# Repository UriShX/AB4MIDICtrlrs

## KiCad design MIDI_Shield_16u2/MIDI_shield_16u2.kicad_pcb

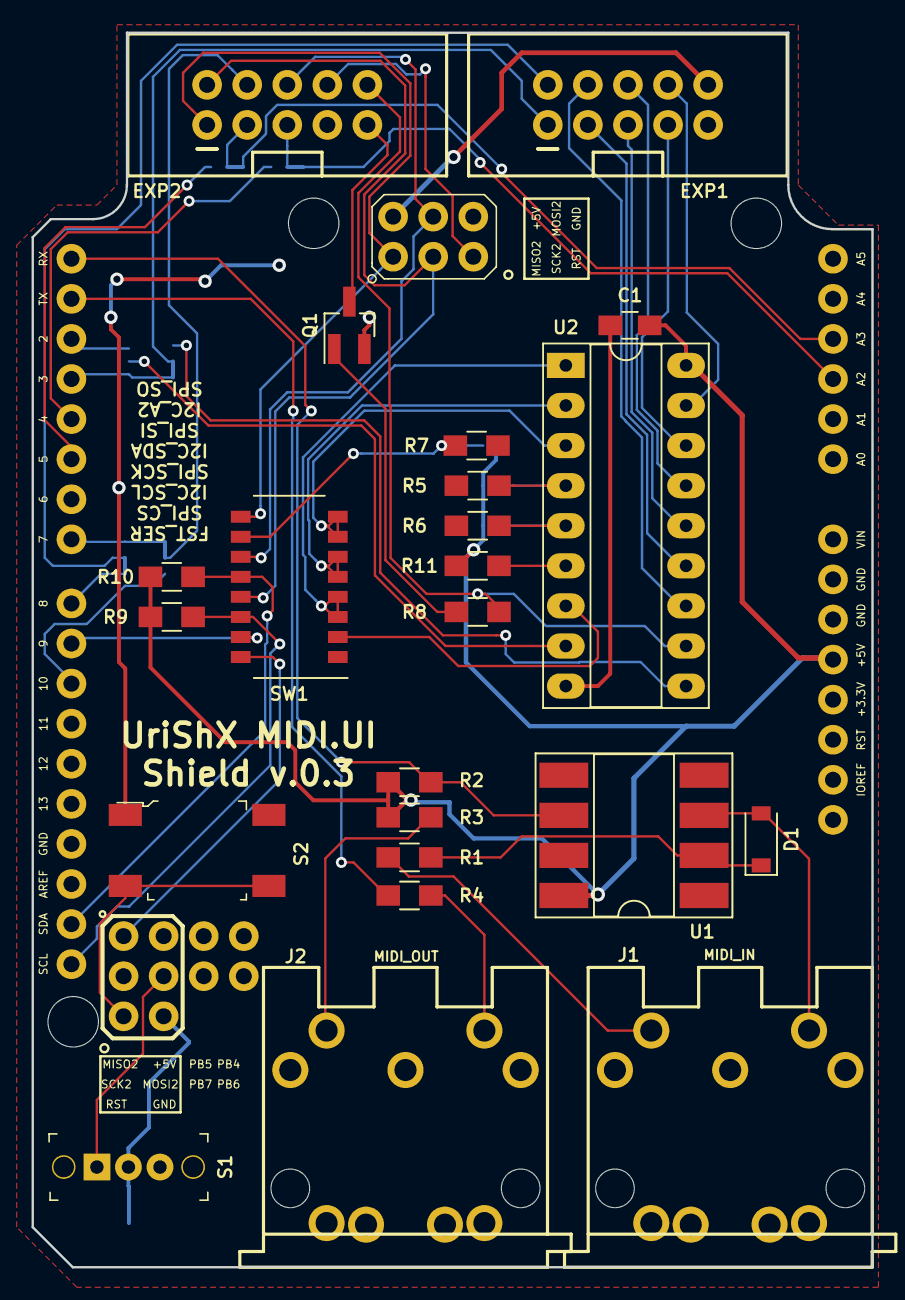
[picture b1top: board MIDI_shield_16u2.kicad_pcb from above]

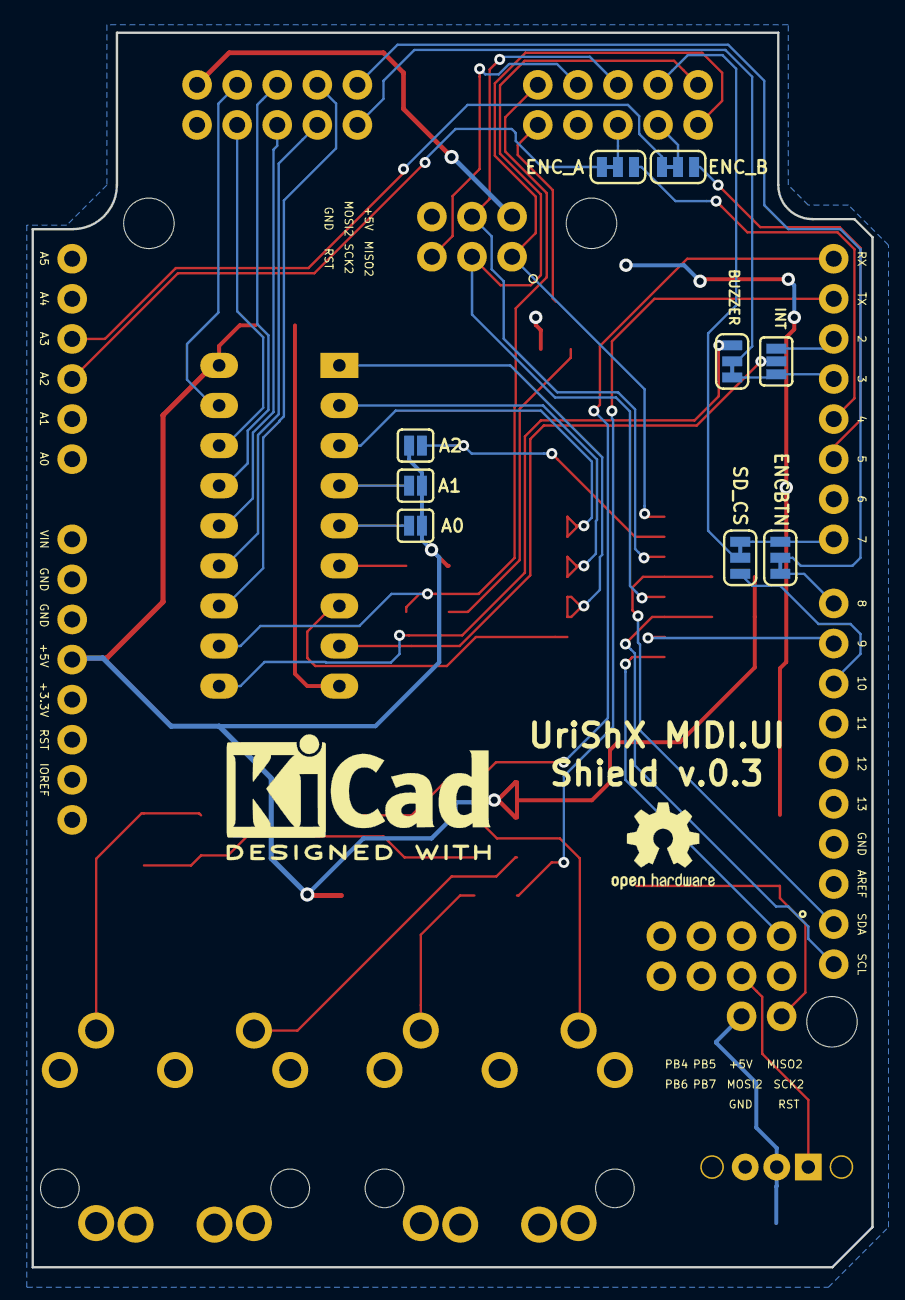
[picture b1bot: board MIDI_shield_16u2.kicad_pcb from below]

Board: 2 copper layers, 53.2 x 78.2 mm, 33 parts (9 on the bottom side), 52 nets.

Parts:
B2: ARDUINO_UNO_R3_SHIELD_ICSP_16u2_BREAKOUT; UNO_R3_SHIELD_16u2_BREAKOUT_wHoles
C1: 0.1UF-0603-25V-_+80_-20%_; C_0805_HandSoldering
D1: 1N4148; D_SOD-123
EXP1, EXP2: CONN_05X2SHD; 2X5-SHROUDED
J1: MIDI_IN; DIN5-RA-PTH
J2: MIDI_OUT; DIN5-RA-PTH
JP1: INT; SMT-JUMPER_3_NO_SILK
JP2: ENC_A; SMT-JUMPER_3_1-NC_TRACE_SILK
JP3: ENC_B; SMT-JUMPER_3_1-NC_TRACE_SILK
JP4: ENCBTN; SMT-JUMPER_3_1-NC_TRACE_SILK
JP5: BUZZER; SMT-JUMPER_3_1-NC_TRACE_SILK
JP6: A0; SMT-JUMPER_2_NO_SILK
JP7: SD_CS; SMT-JUMPER_3_1-NC_TRACE_SILK
JP8: A1; SMT-JUMPER_2_NO_SILK
JP9: A2; SMT-JUMPER_2_NO_SILK
Q1: Q_NPN_BEC_2222A; SOT-23_Handsoldering
R1, R2, R3, R4: 220R_1_4W_5%; R_0805_HandSoldering
R5, R6, R7, R8, R11: 10k_1_4W_5%; R_0805_HandSoldering
R9, R10: 4K7_1_4W_5%; R_0805_HandSoldering
S1: SWITCH-SPDT-SMD-RIGHT-ANGLE; Switch_Slide_Right_Angle_8.6X4.4mm_C&K_OS102011MA1QS1
S2: MOMENTARY-SWITCH-SPST-2-SMD-5.2MM; Switch_Tact_SMD_6x6mm
SW1: SW_DIP_x08; SW_DIP_x8_W6.15mm_Slide_Omron_A6H
U1: OPTO_DARL_6N138S; DIP-8_W8.89mm_SMDSocket_LongPads
U2: MCP23S08; DIP-18_W7.62mm_Socket_LongPads

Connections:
/16U2_RSTJP: B2.SI_2, S1.1
/ARDUINO_RST: B2.RES, B2.RST, EXP2.8
/BUZZER: EXP1.1, JP5.2
/BUZZER_: JP5.1, U2.10
/ENC_A: EXP2.5, JP2.2
/ENC_A_NC: B2.A2, JP2.3
/ENC_A_NO: B2.D4, JP2.1
/ENC_B: EXP2.3, JP3.2
/ENC_BTN: EXP1.2, JP4.2
/ENC_BTN_NC: B2.D8, JP4.3
/ENC_B_NC: B2.A3, JP3.3
/ENC_B_NO: B2.D5, JP3.1
/EXPANDER_CS: SW1.2, U2.7
/EXT_INT0: B2.D2, JP1.3
/EXT_INT1: B2.D3, JP1.1, JP5.3
/FAST_SERIAL: B2.SO_2, SW1.16
/GND_CTL: EXP2.10, R8.2, U2.11
/LCD4: EXP1.5, U2.14
/LCD5: EXP1.6, U2.15
/LCD6: EXP1.7, U2.16
/LCD7: EXP1.8, U2.17
/LCD&BUZZER_CS: B2.D9, SW1.15
/LCDE: EXP1.3, U2.13
/LCDRS: EXP1.4, U2.12
/LCD_GND_CTL: EXP2.9, Q1.3
/MIDI_IN: B2.RX, R2.1, U1.6
/MIDI_OUT: B2.TX, R4.2
/MISO_: B2.D12, B2.MISO, EXP2.1, SW1.9
/MOSI_: B2.D11, B2.MOSI, EXP2.6, SW1.11
/SCK_: B2.D13, B2.SCK, EXP2.2, SW1.13
/SCL: B2.SCL, R9.2, SW1.14
/SDA: B2.SDA, R10.2, SW1.12
/SD_CS: EXP2.4, JP7.2
/SD_CS_NC/ENC_BTN_NO: B2.D7, JP4.1, JP7.3
/SD_CS_NO: B2.D10, JP7.1
GND: B2.GND2, B2.GND@, B2.GND_, C1.2, EXP1.9, J2.2, Q1.2, R5.2, R6.2, R7.2, S1.2, S2.1, S2.2, SW1.1, U1.5, U2.9
unnamed: B2.RST2, S2.3, S2.4
unnamed: D1.1, R1.2, U1.2
unnamed: D1.2, J1.4, U1.3
unnamed: J1.5, R1.1
unnamed: J2.4, R4.1
unnamed: J2.5, R3.1
unnamed: JP1.2, U2.8
unnamed: JP6.1, R6.1, U2.5
unnamed: JP8.1, R5.1, U2.4
unnamed: JP9.2, R7.1, SW1.10
unnamed: Q1.1, R8.1
unnamed: R11.2, U2.6
unnamed: SW1.3, SW1.4, U2.1
unnamed: SW1.5, SW1.6, U2.2
unnamed: SW1.7, SW1.8, U2.3
VCC: B2.5V, B2.5V_1, B2.5V_2, C1.1, EXP1.10, JP6.2, JP8.2, JP9.1, R2.2, R3.2, R9.1, R10.1, R11.1, U1.8, U2.18

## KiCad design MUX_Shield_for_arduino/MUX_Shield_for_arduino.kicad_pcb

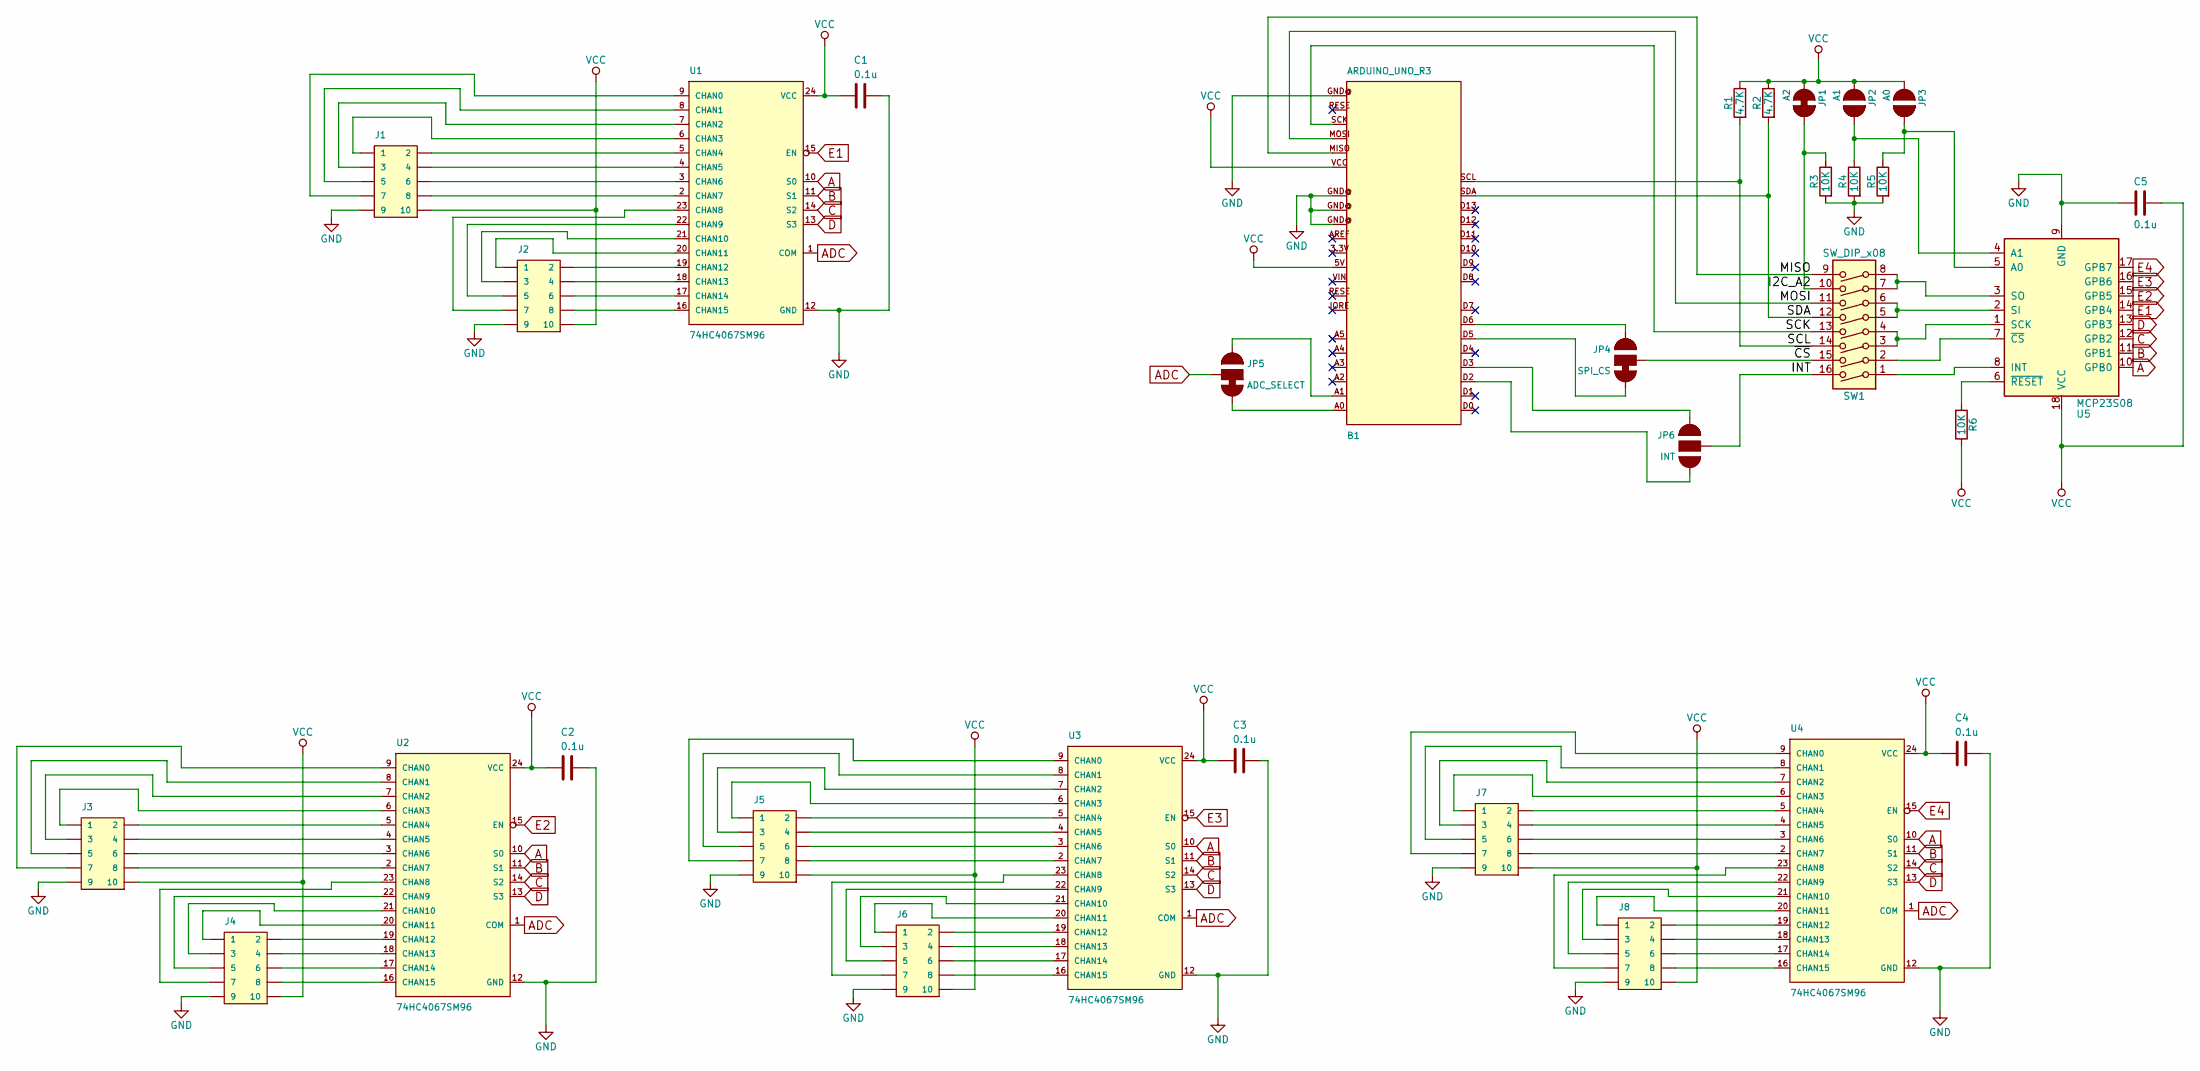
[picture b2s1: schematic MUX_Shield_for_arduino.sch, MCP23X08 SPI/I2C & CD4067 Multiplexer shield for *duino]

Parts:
B1: ARDUINO_UNO_R3; ARDUINO_R3
C1, C2, C3, C4, C5: 0.1u; C_0805_HandSoldering
J1, J2, J3, J4, J5, J6, J7, J8: CONN_05X20.05_IN_PTH_SILK; 2X5-SHROUDED
JP1: A2; SMT-JUMPER_2_NC_TRACE_SILK
JP2: A1; SMT-JUMPER_2_NO_SILK
JP3: A0; SMT-JUMPER_2_NO_SILK
JP4: SPI_CS; SMT-JUMPER_3_1-NC_TRACE_SILK
JP5: ADC_SELECT; SMT-JUMPER_3_1-NC_TRACE_SILK
JP6: INT; SMT-JUMPER_3_NO_SILK
R1, R2: 4.7K; R_0805_HandSoldering
R3, R4, R5, R6: 10K; R_0805_HandSoldering
SW1: SW_DIP_x08; SW_DIP_x8_W6.15mm_Slide_Omron_A6H
U1, U2, U3, U4: 74HC4067SM96; SOIC-24W_7.5x15.4mm_Pitch1.27mm
U5: MCP23S08; DIP-18_W7.62mm_Socket_LongPads

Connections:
/I2C_A2: JP1.2, R3.1, SW1.10
/INT: JP6.2, SW1.16
/MISO: B1.MISO, SW1.9
/MOSI: B1.MOSI, SW1.11
/SCK: B1.SCK, SW1.13
/SCL: B1.SCL, R1.2, SW1.14
/SDA: B1.SDA, R2.2, SW1.12
/~CS: JP4.2, SW1.15
A: U1.10 (S0), U2.10 (S0), U3.10 (S0), U4.10 (S0), U5.10 (GPB0)
ADC: JP5.2, U1.1 (COM), U2.1 (COM), U3.1 (COM), U4.1 (COM)
B: U1.11 (S1), U2.11 (S1), U3.11 (S1), U4.11 (S1), U5.11 (GPB1)
C: U1.14 (S2), U2.14 (S2), U3.14 (S2), U4.14 (S2), U5.12 (GPB2)
D: U1.13 (S3), U2.13 (S3), U3.13 (S3), U4.13 (S3), U5.13 (GPB3)
E1: U1.15 (EN), U5.14 (GPB4)
E2: U2.15 (EN), U5.15 (GPB5)
E3: U3.15 (EN), U5.16 (GPB6)
E4: U4.15 (EN), U5.17 (GPB7)
GND: B1.GND@ (GND), C1.1, C2.1, C3.1, C4.1, C5.2, J1.9, J2.9, J3.9, J4.9, J5.9, J6.9, J7.9, J8.9, R3.2, R4.2, R5.2, U1.12 (GND), U2.12 (GND), U3.12 (GND), U4.12 (GND), U5.9 (GND)
unnamed: B1.A0, JP5.3
unnamed: B1.A1, JP5.1
unnamed: B1.D2, JP6.3
unnamed: B1.D3 (*D3), JP6.1
unnamed: B1.D5 (*D5), JP4.3
unnamed: B1.D6 (*D6), JP4.1
unnamed: J1.1, U1.6 (CHAN3)
unnamed: J1.2, U1.5 (CHAN4)
unnamed: J1.3, U1.7 (CHAN2)
unnamed: J1.4, U1.4 (CHAN5)
unnamed: J1.5, U1.8 (CHAN1)
unnamed: J1.6, U1.3 (CHAN6)
unnamed: J1.7, U1.9 (CHAN0)
unnamed: J1.8, U1.2 (CHAN7)
unnamed: J2.1, U1.20 (CHAN11)
unnamed: J2.2, U1.19 (CHAN12)
unnamed: J2.3, U1.21 (CHAN10)
unnamed: J2.4, U1.18 (CHAN13)
unnamed: J2.5, U1.22 (CHAN9)
unnamed: J2.6, U1.17 (CHAN14)
unnamed: J2.7, U1.23 (CHAN8)
unnamed: J2.8, U1.16 (CHAN15)
unnamed: J3.1, U2.6 (CHAN3)
unnamed: J3.2, U2.5 (CHAN4)
unnamed: J3.3, U2.7 (CHAN2)
unnamed: J3.4, U2.4 (CHAN5)
unnamed: J3.5, U2.8 (CHAN1)
unnamed: J3.6, U2.3 (CHAN6)
unnamed: J3.7, U2.9 (CHAN0)
unnamed: J3.8, U2.2 (CHAN7)
unnamed: J4.1, U2.20 (CHAN11)
unnamed: J4.2, U2.19 (CHAN12)
unnamed: J4.3, U2.21 (CHAN10)
unnamed: J4.4, U2.18 (CHAN13)
unnamed: J4.5, U2.22 (CHAN9)
unnamed: J4.6, U2.17 (CHAN14)
unnamed: J4.7, U2.23 (CHAN8)
unnamed: J4.8, U2.16 (CHAN15)
unnamed: J5.1, U3.6 (CHAN3)
unnamed: J5.2, U3.5 (CHAN4)
unnamed: J5.3, U3.7 (CHAN2)
unnamed: J5.4, U3.4 (CHAN5)
unnamed: J5.5, U3.8 (CHAN1)
unnamed: J5.6, U3.3 (CHAN6)
unnamed: J5.7, U3.9 (CHAN0)
unnamed: J5.8, U3.2 (CHAN7)
unnamed: J6.1, U3.20 (CHAN11)
unnamed: J6.2, U3.19 (CHAN12)
unnamed: J6.3, U3.21 (CHAN10)
unnamed: J6.4, U3.18 (CHAN13)
unnamed: J6.5, U3.22 (CHAN9)
unnamed: J6.6, U3.17 (CHAN14)
unnamed: J6.7, U3.23 (CHAN8)
unnamed: J6.8, U3.16 (CHAN15)
unnamed: J7.1, U4.6 (CHAN3)
unnamed: J7.2, U4.5 (CHAN4)
unnamed: J7.3, U4.7 (CHAN2)
unnamed: J7.4, U4.4 (CHAN5)
unnamed: J7.5, U4.8 (CHAN1)
unnamed: J7.6, U4.3 (CHAN6)
unnamed: J7.7, U4.9 (CHAN0)
unnamed: J7.8, U4.2 (CHAN7)
unnamed: J8.1, U4.20 (CHAN11)
unnamed: J8.2, U4.19 (CHAN12)
unnamed: J8.3, U4.21 (CHAN10)
unnamed: J8.4, U4.18 (CHAN13)
unnamed: J8.5, U4.22 (CHAN9)
unnamed: J8.6, U4.17 (CHAN14)
unnamed: J8.7, U4.23 (CHAN8)
unnamed: J8.8, U4.16 (CHAN15)
unnamed: JP2.2, R4.1, U5.4 (A1)
unnamed: JP3.2, R5.1, U5.5 (A0)
unnamed: R6.2, U5.6 (~RESET)
unnamed: SW1.1, U5.8 (INT)
unnamed: SW1.2, U5.7 (~CS)
unnamed: SW1.3, SW1.4, U5.1 (SCK)
unnamed: SW1.5, SW1.6, U5.2 (SI)
unnamed: SW1.7, SW1.8, U5.3 (SO)
VCC: B1.5V, B1.VCC, C1.2, C2.2, C3.2, C4.2, C5.1, J1.10, J2.10, J3.10, J4.10, J5.10, J6.10, J7.10, J8.10, JP1.1, JP2.1, JP3.1, R1.1, R2.1, R6.1, U1.24 (VCC), U2.24 (VCC), U3.24 (VCC), U4.24 (VCC), U5.18 (VCC)

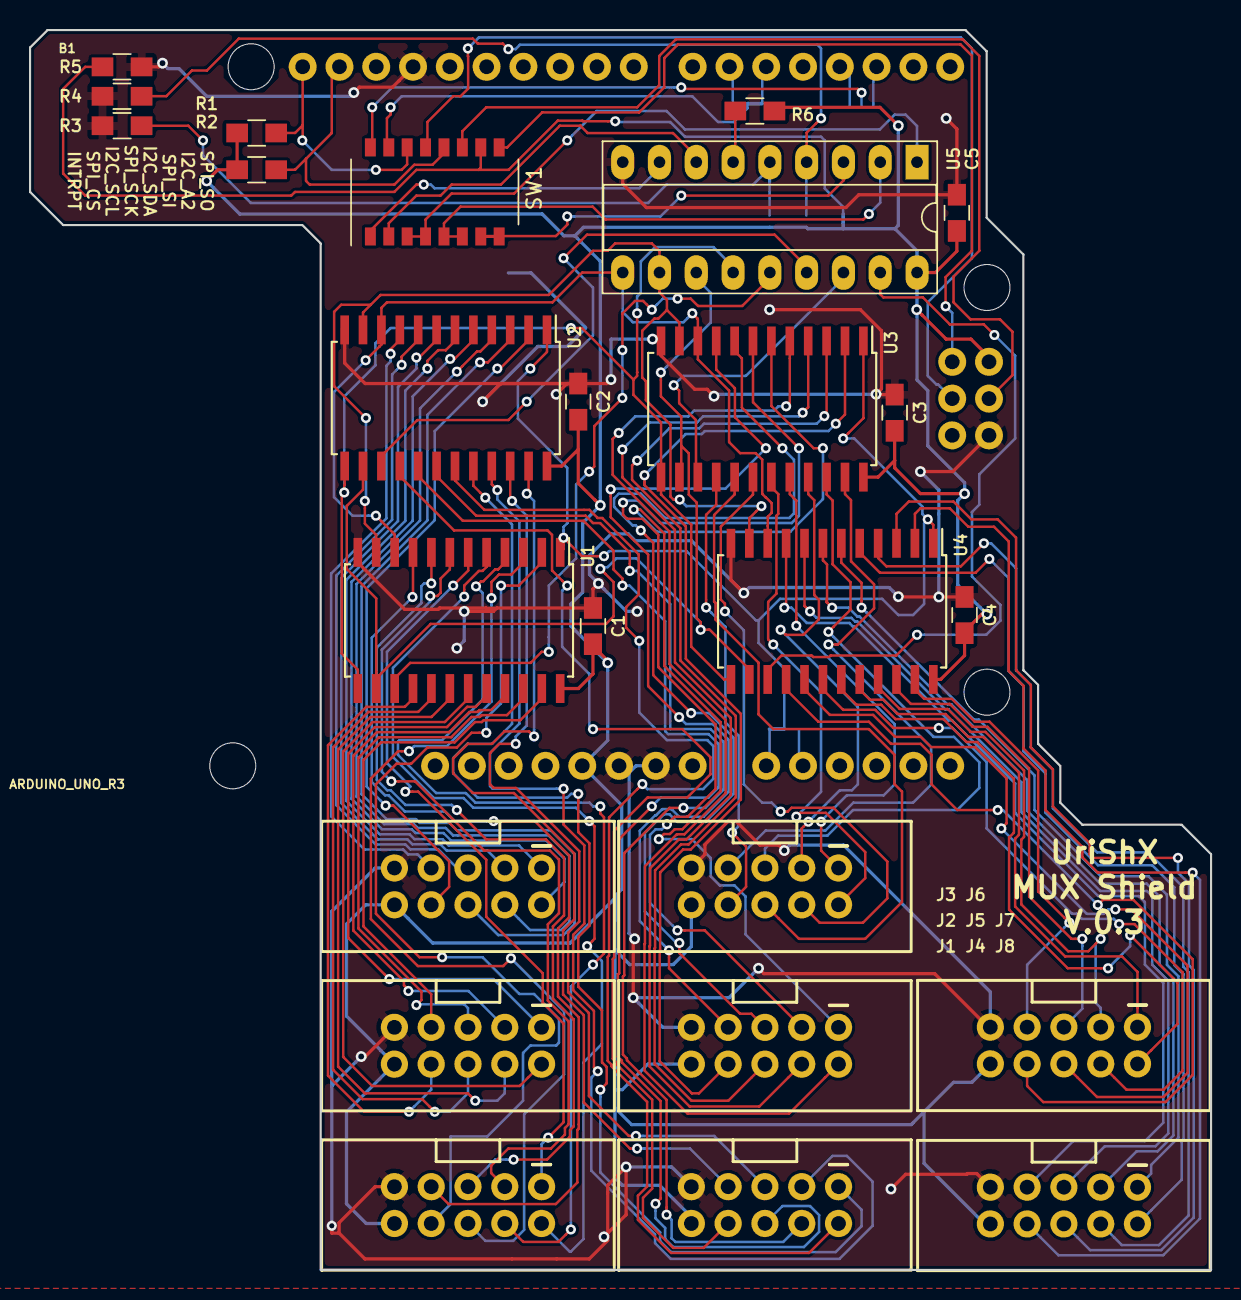
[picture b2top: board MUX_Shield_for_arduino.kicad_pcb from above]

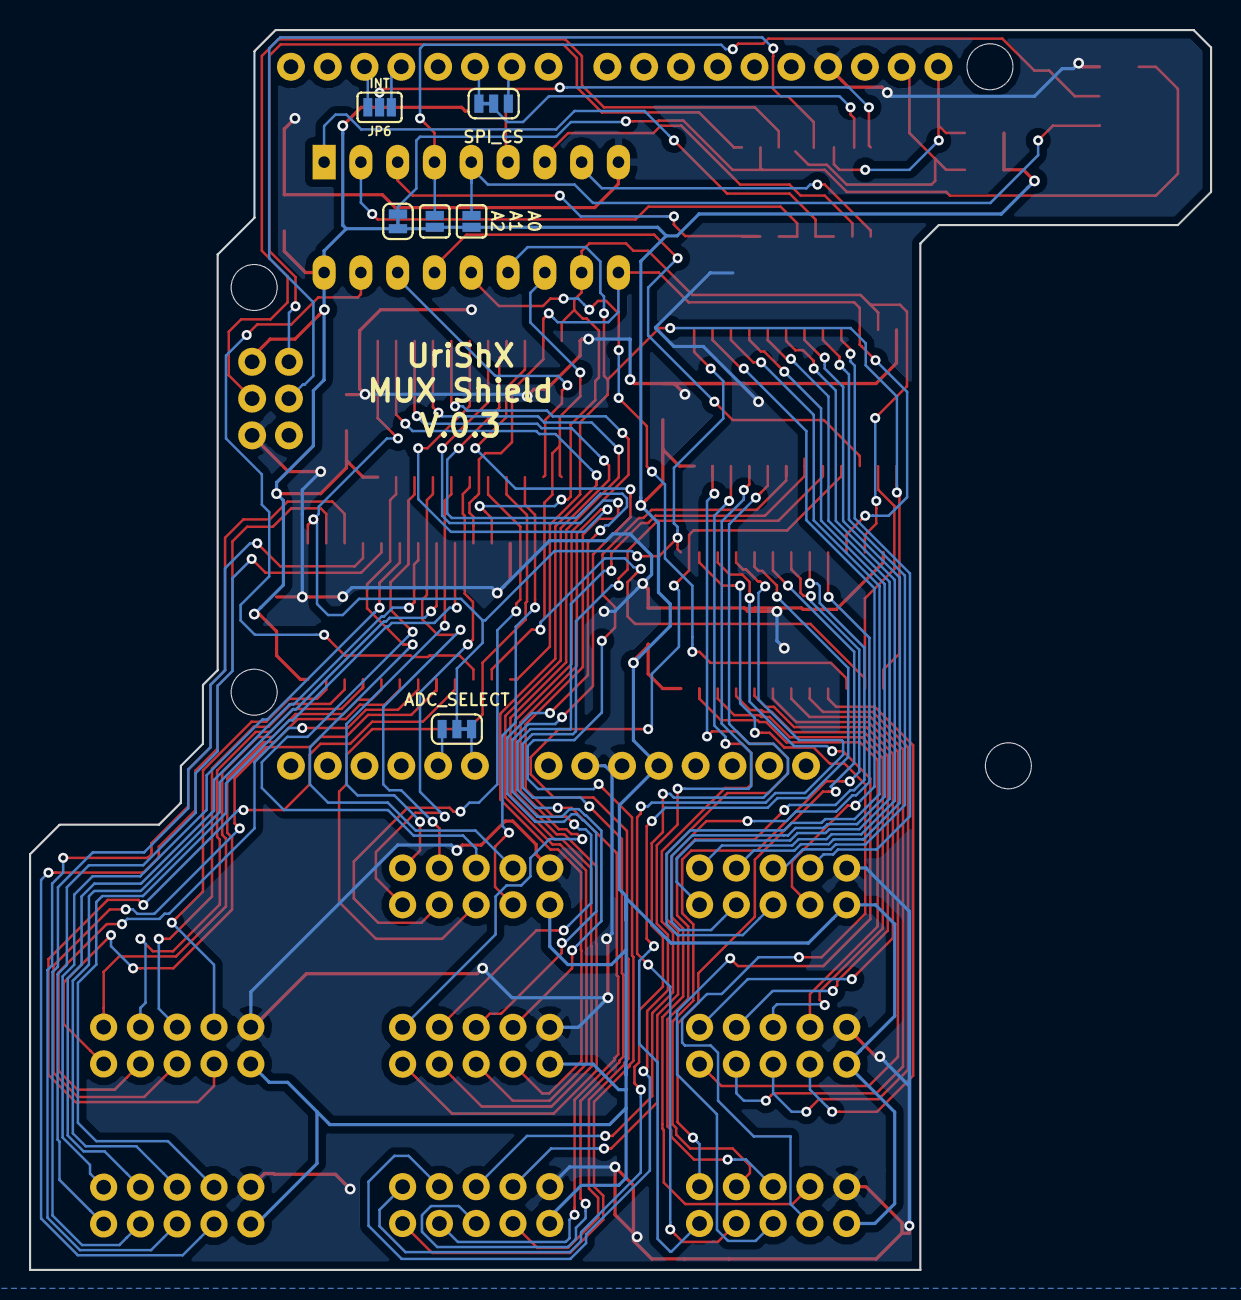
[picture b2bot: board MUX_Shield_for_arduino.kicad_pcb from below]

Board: 2 copper layers, 81.5 x 85.6 mm, 32 parts (6 on the bottom side), 97 nets.

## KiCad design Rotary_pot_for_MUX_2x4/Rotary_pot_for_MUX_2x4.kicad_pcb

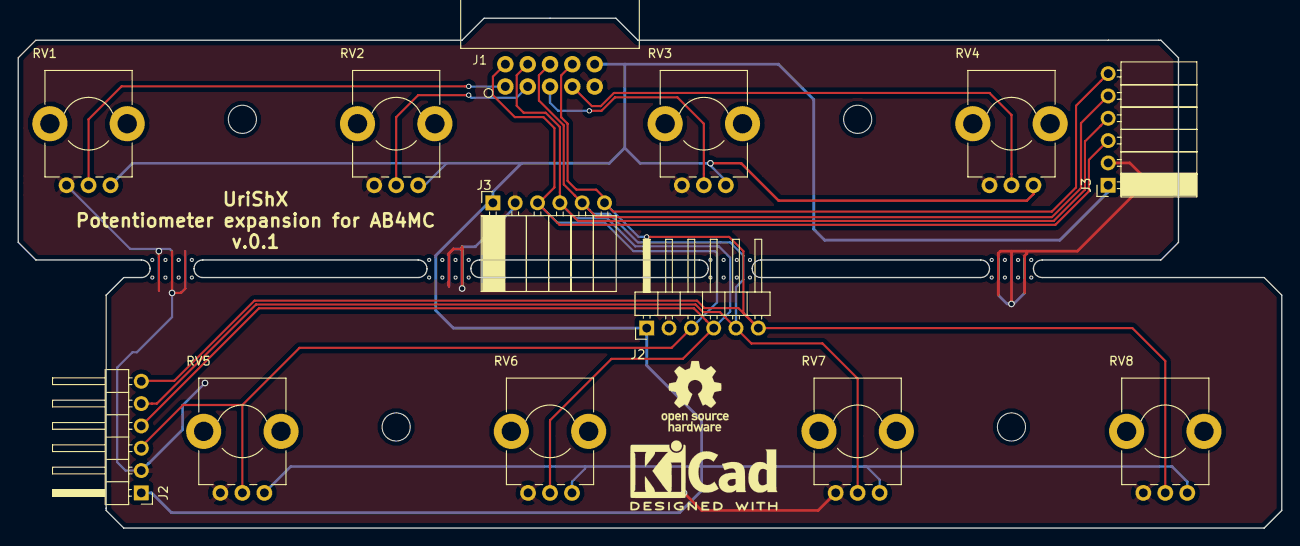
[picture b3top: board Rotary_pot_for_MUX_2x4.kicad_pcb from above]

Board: 2 copper layers, 143.8 x 58.0 mm, 13 parts (0 on the bottom side), 10 nets.

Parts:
J1: Conn_02x05_Odd_Even; 2X5-SHROUDED_rightAngle
J2, J2#2: Conn_01x06_Male; Pin_Header_Angled_1x06_Pitch2.54mm
J3, J3#2: Conn_01x06_Female; Socket_Strip_Angled_1x06_Pitch2.54mm
RV1, RV2, RV3, RV4, RV5, RV6, RV7, RV8: 10k_B; Potentiometer_Bourns_PTV09A_Horizontal

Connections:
GND: J1.9, J2.2, J2#2.2, J3.2, J3#2.2, RV1.1, RV2.1, RV3.1, RV4.1, RV5.1, RV6.1, RV7.1, RV8.1
unnamed: J1.1, RV1.2
unnamed: J1.2, J2.3, J2#2.3, J3.3, J3#2.3, RV5.2
unnamed: J1.3, RV2.2
unnamed: J1.4, J2.4, J2#2.4, J3.4, J3#2.4, RV6.2
unnamed: J1.5, RV3.2
unnamed: J1.6, J2.5, J2#2.5, J3.5, J3#2.5, RV7.2
unnamed: J1.7, RV4.2
unnamed: J1.8, J2.6, J2#2.6, J3.6, J3#2.6, RV8.2
VCC: J1.10, J2.1, J2#2.1, J3.1, J3#2.1, RV1.3, RV2.3, RV3.3, RV4.3, RV5.3, RV6.3, RV7.3, RV8.3

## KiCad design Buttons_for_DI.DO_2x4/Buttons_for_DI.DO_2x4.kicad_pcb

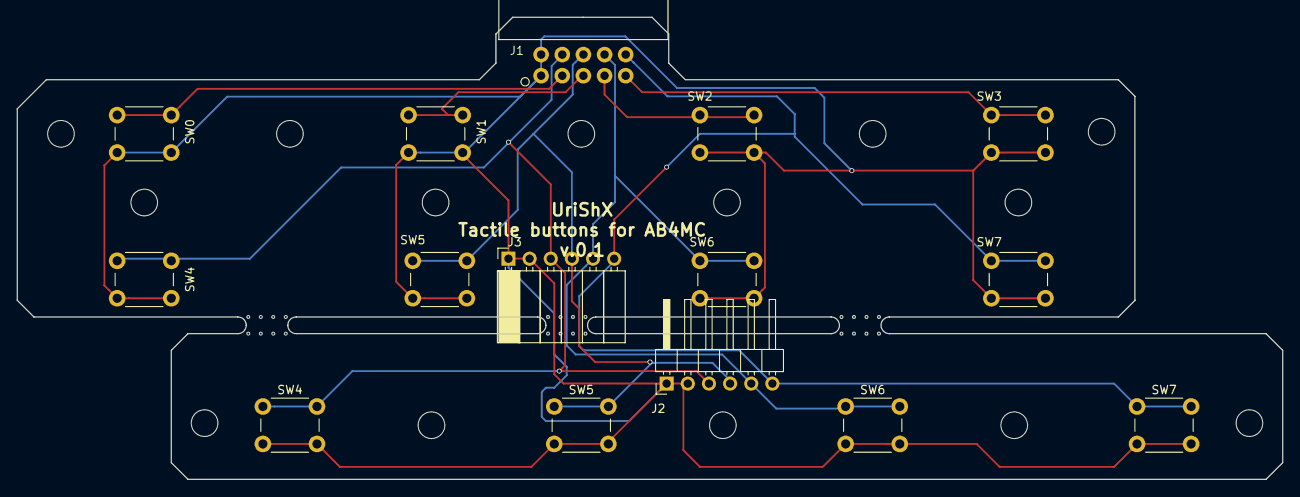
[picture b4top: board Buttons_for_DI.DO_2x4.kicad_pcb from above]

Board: 2 copper layers, 152.0 x 55.5 mm, 15 parts (0 on the bottom side), 9 nets.

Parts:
J1: Conn_02x05_Odd_Even; 2X5-SHROUDED_rightAngle
J2: Conn_01x06_Male; Pin_Header_Angled_1x06_Pitch2.54mm
J3: Conn_01x06_Female; Socket_Strip_Angled_1x06_Pitch2.54mm
SW0, SW1, SW2, SW3, SW4, SW4#2, SW5, SW5#2, SW6, SW6#2, SW7, SW7#2: SW_Push; SW_PUSH_6mm

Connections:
Common_pin: J1.1, J1.2, J2.1, J2.2, J3.1, J3.2, SW0.2, SW1.2, SW2.2, SW3.2, SW4.2, SW4#2.2, SW5.2, SW5#2.2, SW6.2, SW6#2.2, SW7.2, SW7#2.2
unnamed: J1.3, SW0.1
unnamed: J1.4, J2.3, J3.3, SW4.1, SW4#2.1
unnamed: J1.5, SW1.1
unnamed: J1.6, J2.4, J3.4, SW5.1, SW5#2.1
unnamed: J1.7, SW2.1
unnamed: J1.8, J2.5, J3.5, SW6.1, SW6#2.1
unnamed: J1.9, SW3.1
unnamed: J1.10, J2.6, J3.6, SW7.1, SW7#2.1

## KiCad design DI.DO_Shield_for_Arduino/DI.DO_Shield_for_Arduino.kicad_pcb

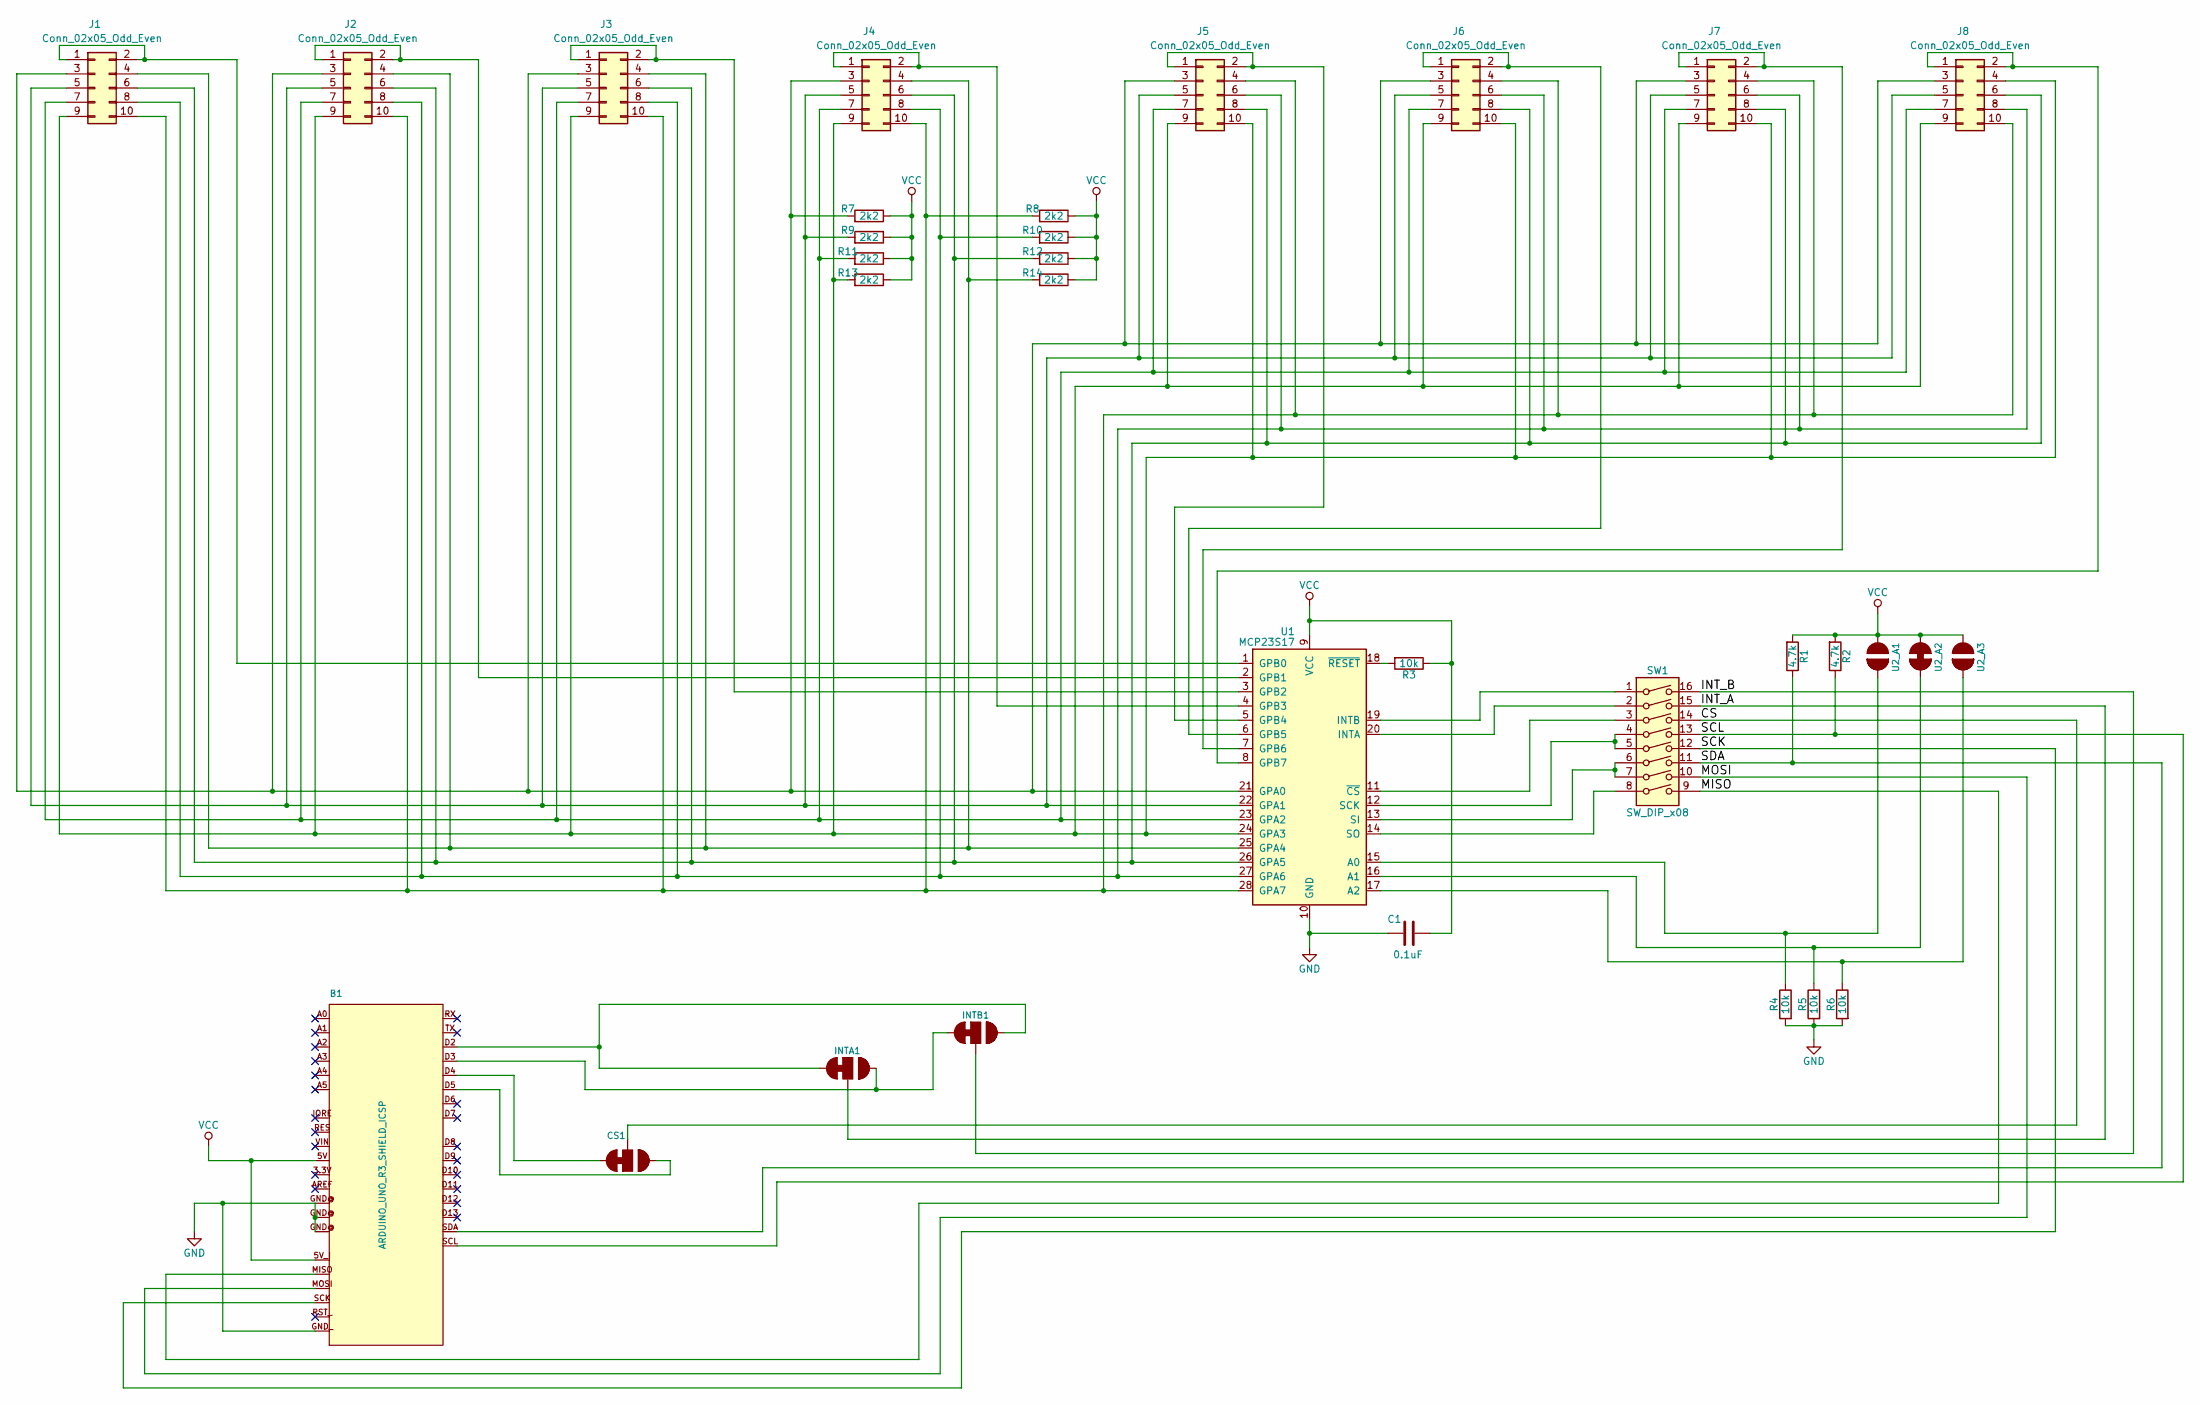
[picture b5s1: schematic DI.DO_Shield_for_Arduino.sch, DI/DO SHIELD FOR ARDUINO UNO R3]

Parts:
B1: ARDUINO_UNO_R3_SHIELD_ICSP; ARDUINO_R3
C1: 0.1uF; C_0805_HandSoldering
CS1: JUMPER-SMT_3_1-NC; SMT-JUMPER_3_1-NC_TRACE_SILK
INTA1: JUMPER-SMT_3_1-NC; SMT-JUMPER_3_1-NC_TRACE_SILK
INTB1: JUMPER-SMT_3_1-NC; SMT-JUMPER_3_1-NC_TRACE_SILK
J1, J2, J3, J4, J5, J6, J7, J8: Conn_02x05_Odd_Even; 2X5-SHROUDED
R1, R2: 4.7k; R_0805_HandSoldering
R3, R4, R5, R6: 10k; R_0805_HandSoldering
R7, R8, R9, R10, R11, R12, R13, R14: 2k2; R_0805_HandSoldering
SW1: SW_DIP_x08; SW_DIP_x8_W6.15mm_Slide_Omron_A6H
U1: MCP23S17; DIP-28_W7.62mm_LongPads
U2_A1, U2_A3: JUMPER-SMT_2_NO; SMT-JUMPER_2_NO_SILK
U2_A2: JUMPER-SMT_2_NC; SMT-JUMPER_2_NC_TRACE_SILK

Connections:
/CS: CS1.2, SW1.14
/INT_A: INTA1.2, SW1.15
/INT_B: INTB1.2, SW1.16
/MISO: B1.MISO, SW1.9
/MOSI: B1.MOSI, SW1.10
/SCK: B1.SCK, SW1.12
/SCL: B1.SCL, R2.1, SW1.13
/SDA: B1.SDA, R1.1, SW1.11
GND: B1.GND@ (GND), B1.GND_ (GND), C1.1, R4.2, R5.2, R6.2, U1.10 (GND)
unnamed: B1.D2, INTA1.3, INTB1.1
unnamed: B1.D3 (*D3), INTA1.1, INTB1.3
unnamed: B1.D4, CS1.3
unnamed: B1.D5 (*D5), CS1.1
unnamed: J1.1, J1.2, U1.1 (GPB0)
unnamed: J1.3, J2.3, J3.3, J4.3, J5.3, J6.3, J7.3, J8.3, R7.2, U1.21 (GPA0)
unnamed: J1.4, J2.4, J3.4, J4.4, R14.2, U1.25 (GPA4)
unnamed: J1.5, J2.5, J3.5, J4.5, J5.5, J6.5, J7.5, J8.5, R9.2, U1.22 (GPA1)
unnamed: J1.6, J2.6, J3.6, J4.6, J5.8, J6.8, J7.8, J8.6, R12.2, U1.26 (GPA5)
unnamed: J1.7, J2.7, J3.7, J4.7, J5.7, J6.7, J7.7, J8.7, R11.2, U1.23 (GPA2)
unnamed: J1.8, J2.8, J3.8, J4.8, J5.6, J6.6, J7.6, J8.8, R10.2, U1.27 (GPA6)
unnamed: J1.9, J2.9, J3.9, J4.9, J5.9, J5.10, J6.9, J6.10, J7.9, J7.10, J8.4, J8.9, R13.2, U1.24 (GPA3)
unnamed: J1.10, J2.10, J3.10, J4.10, J5.4, J6.4, J7.4, J8.10, R8.2, U1.28 (GPA7)
unnamed: J2.1, J2.2, U1.2 (GPB1)
unnamed: J3.1, J3.2, U1.3 (GPB2)
unnamed: J4.1, J4.2, U1.4 (GPB3)
unnamed: J5.1, J5.2, U1.5 (GPB4)
unnamed: J6.1, J6.2, U1.6 (GPB5)
unnamed: J7.1, J7.2, U1.7 (GPB6)
unnamed: J8.1, J8.2, U1.8 (GPB7)
unnamed: R3.2, U1.18 (~RESET)
unnamed: R4.1, U1.15 (A0), U2_A1.2
unnamed: R5.1, U1.16 (A1), U2_A2.2
unnamed: R6.1, U1.17 (A2), U2_A3.2
unnamed: SW1.1, U1.19 (INTB)
unnamed: SW1.2, U1.20 (INTA)
unnamed: SW1.3, U1.11 (~CS)
unnamed: SW1.4, SW1.5, U1.12 (SCK)
unnamed: SW1.6, SW1.7, U1.13 (SI)
unnamed: SW1.8, U1.14 (SO)
VCC: B1.5V, B1.5V_I (VCC), C1.2, R1.2, R2.2, R3.1, R7.1, R8.1, R9.1, R10.1, R11.1, R12.1, R13.1, R14.1, U1.9 (VCC), U2_A1.1, U2_A2.1, U2_A3.1

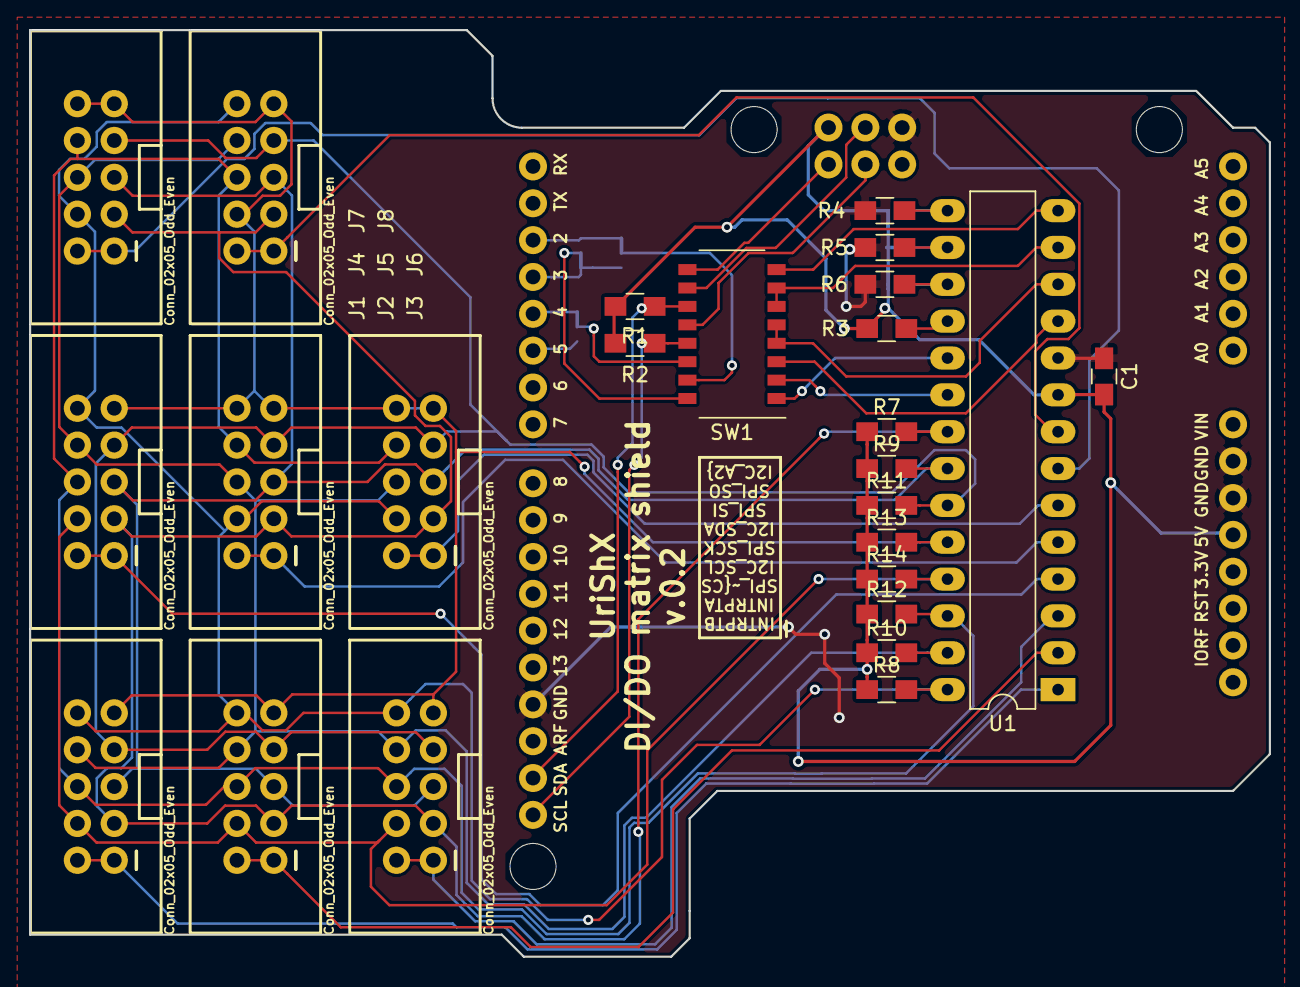
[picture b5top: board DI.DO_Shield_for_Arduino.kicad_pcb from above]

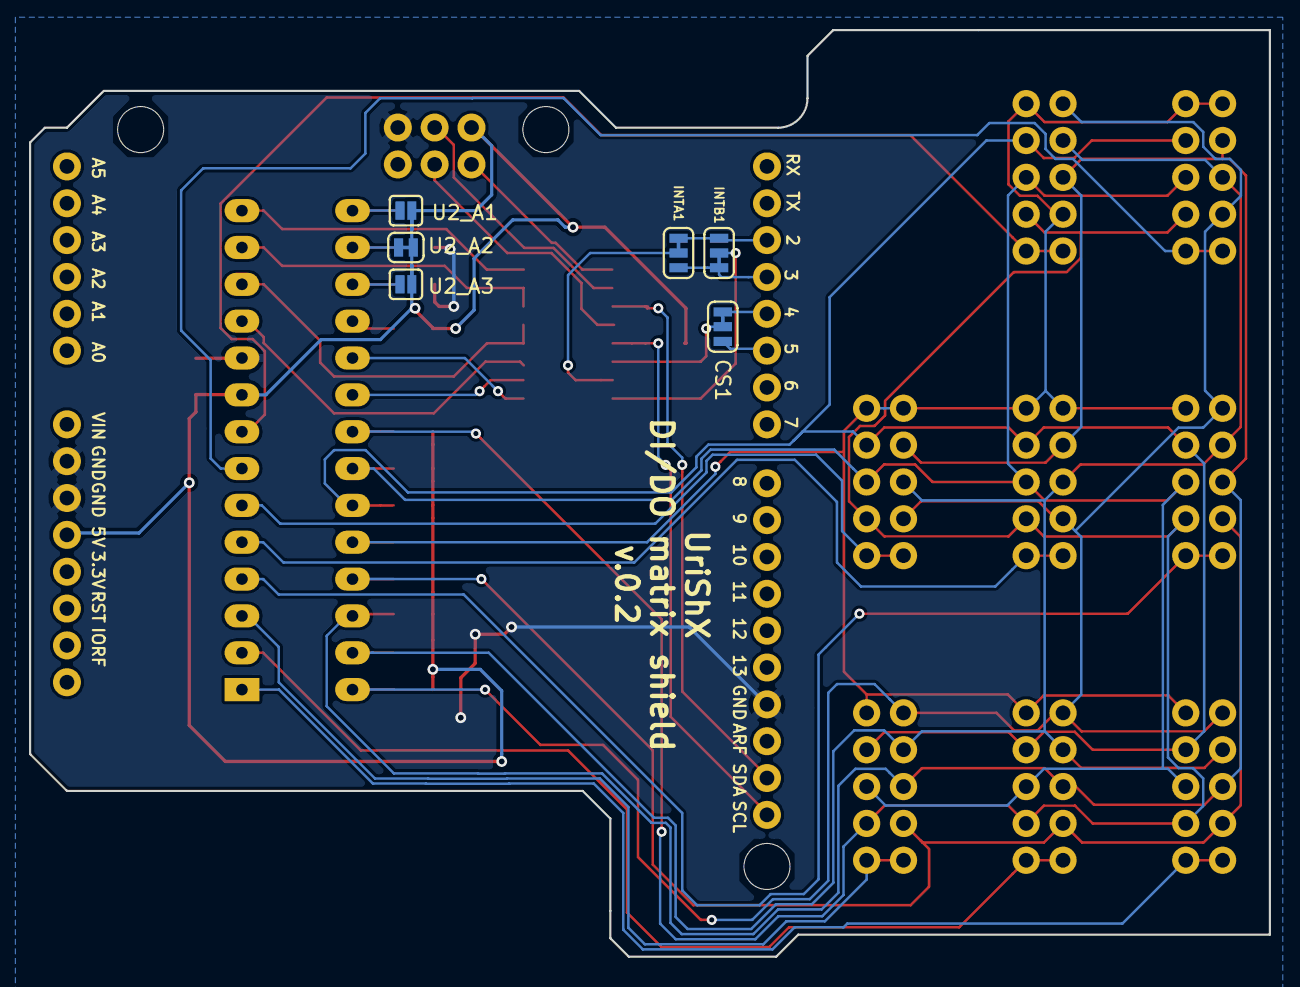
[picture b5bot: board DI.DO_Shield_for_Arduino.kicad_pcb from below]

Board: 2 copper layers, 85.5 x 63.9 mm, 32 parts (6 on the bottom side), 40 nets.
